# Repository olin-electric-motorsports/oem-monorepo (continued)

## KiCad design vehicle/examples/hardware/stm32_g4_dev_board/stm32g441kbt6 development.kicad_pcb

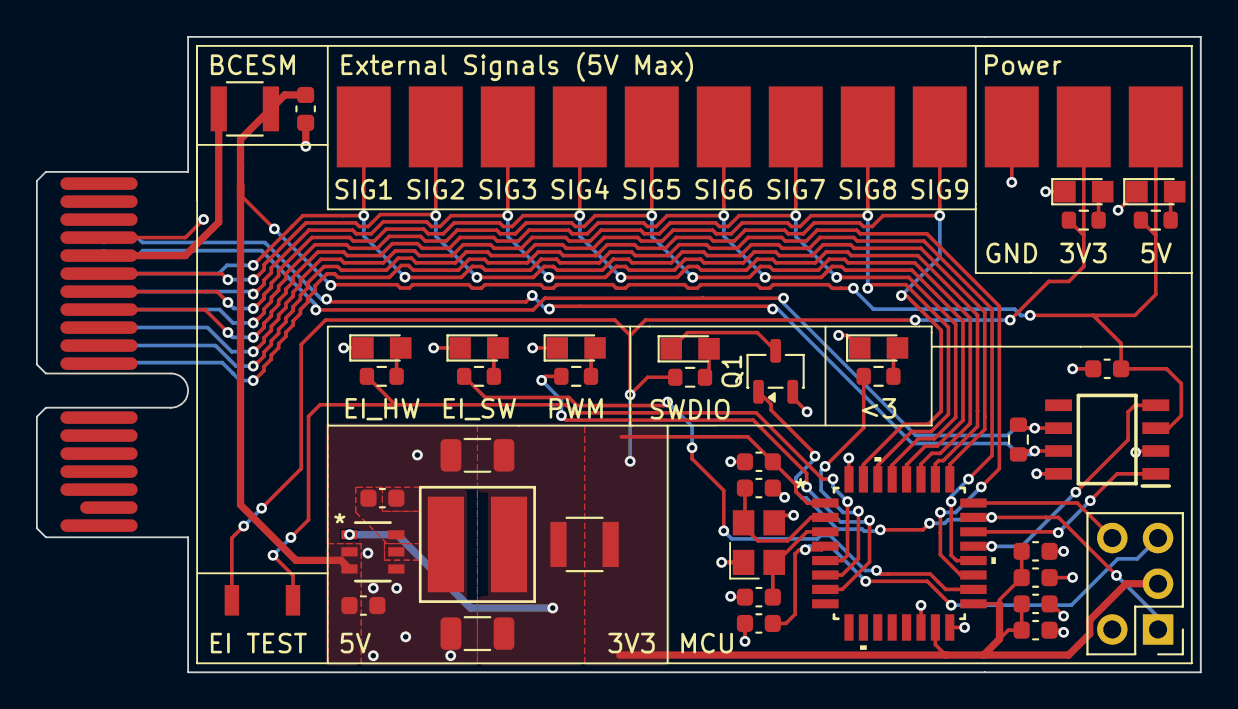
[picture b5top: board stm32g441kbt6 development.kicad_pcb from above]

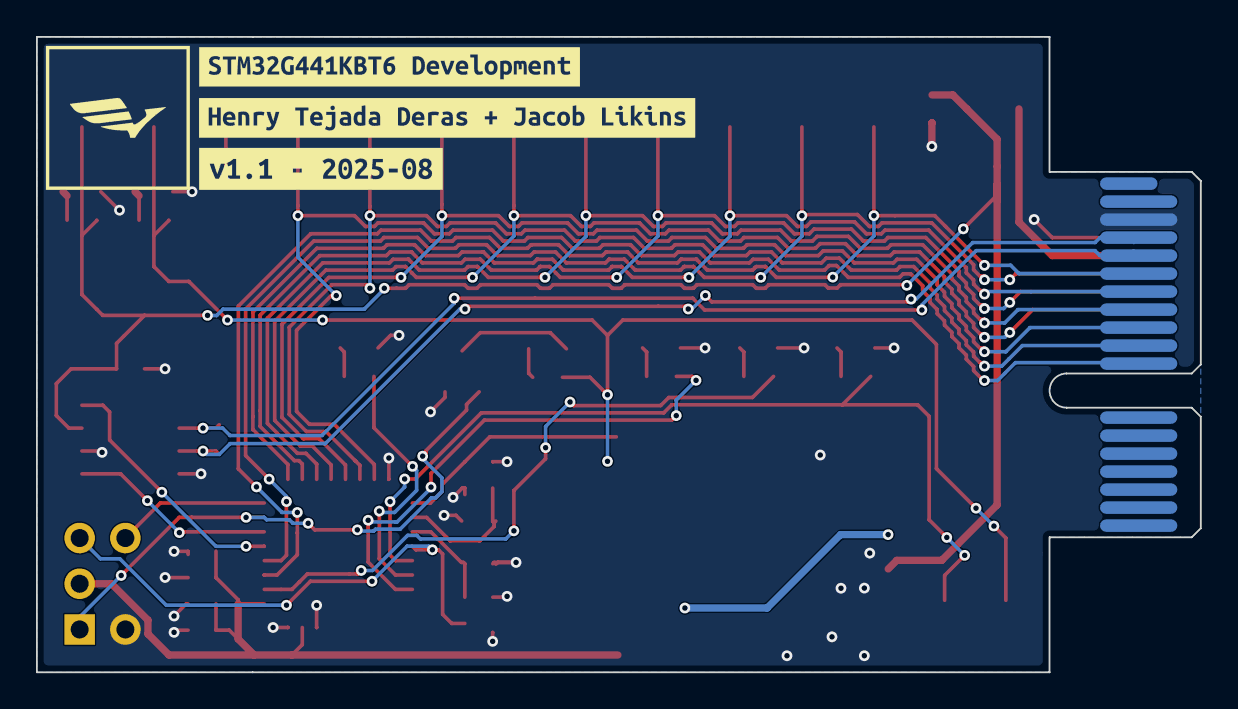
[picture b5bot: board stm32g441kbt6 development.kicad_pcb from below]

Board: 2 copper layers, 64.7 x 35.3 mm, 55 parts (3 on the bottom side), 37 nets.

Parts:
C1, C2, C5, C6, C11: C_0.1uF; C_0603
C3: C_10nF; C_0603
C4: C_1uF; C_0603
C7: C_4.7uF; C_0603
C8, C12: C_10uF; C_0603
C9, C10: C_22uF; C_1206_3216Metric
C13, C14: C_30pF; C_0603
D1: 3V3 POWER; CHIPLED_0805
D2: 5V POWER; CHIPLED_0805
D3: HEARTBEAT; CHIPLED_0805
D5: SWDIO; CHIPLED_0805
D6: INTERRUPT_TEST_HW; CHIPLED_0805
D7: INTERRUPT_TEST_SW; CHIPLED_0805
D8: PWM_TEST; CHIPLED_0805
F1, F2: F_500mA_16V; Fuse_1210
J1: CONN_pcie_x1; pcie_x1
J2: Programming_Pin_Header; Programming_Pin_Header_Keyed
L1: L_3.9uH; IND_BOURNS_SRR5018
Q1: BSS138; SOT-23-3
R1: R_120; R_0603
R2, R3, R4, R6, R7, R8, R9: R_1K; R_0603
SW1: INTERRUPT TEST SWITCH; SW_B3U-1000P_4.2x1.7mm
TP1: 3V3; Test_Point_SMD
TP2: 5V; Test_Point_SMD
TP3: EXT_SIG_1; Test_Point_SMD
TP4: EXT_SIG_2; Test_Point_SMD
TP5: EXT_SIG_3; Test_Point_SMD
TP6: EXT_SIG_4; Test_Point_SMD
TP7: EXT_SIG_5; Test_Point_SMD
TP8: EXT_SIG_6; Test_Point_SMD
TP9: EXT_SIG_7; Test_Point_SMD
TP10: EXT_SIG_8; Test_Point_SMD
TP11: EXT_SIG_9; Test_Point_SMD
TP12: GND; Test_Point_SMD
U1: STM32G441KBT6
U2: MCP2561-E_SN; SOIC127P600X175-8N
U3: AP63203WU-7; AP63203WU-7_DIO
Y1: X_Crystal_16MHz_18pF; Crystal_TXC7M
kibuzzard-68A62DAB: G***; kibuzzard-68A62DAB
kibuzzard-68A62DD1: G***; kibuzzard-68A62DD1
kibuzzard-68A78CB4: G***; kibuzzard-68A78CB4

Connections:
+3V3: C3.1, C4.1, C5.1, C6.1, C7.1, F2.2, J2.3, R2.1, R6.1, SW1.1, TP1.1, U1.1 (VDD), U1.15 (VDDA), U1.17 (VDD)
+5V: C1.2, C8.1, C12.1, F1.1, R3.1, TP2.1, U2.3 (VDD), U3.2 (EN), U3.3 (VIN)
/CAN_+: J1.A4 (CAN+), R1.1, U2.7 (CANH)
/CAN_-: J1.A5 (CAN-), R1.2, U2.6 (CANL)
/CAN_RX: U1.21 ((FDCAN1_RX/GPIO_EXTI11)PA11), U2.4 (RXD)
/CAN_TX: U1.22 ((FDCAN1_TX/GPIO_EXTI12)PA12), U2.1 (TXD)
/EXTERNAL_SIGNAL_1: J1.A6 (io_0), TP3.1, U1.19 ((TIM2_CH3/TIM15_BKIN/USART1_TX/GPIO_EXT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)
/EXTERNAL_SIGNAL_2: J1.B6 (io_1), TP4.1, U1.20 ((TIM2_CH4/USART1_RX/TIM17_BKIN/GPIO_EXT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)
/EXTERNAL_SIGNAL_3: J1.A7 (io_2), TP5.1, U1.25 ((TIM2_ETR/TIM2_CH1/GPIO_EXTI15)PA15)
/EXTERNAL_SIGNAL_4: J1.B7 (io_3), TP6.1, U1.26 ((TIM3_ETR/SPI1_SCK/TIM4_ETR/TIM2_CH2/GP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)
/EXTERNAL_SIGNAL_5: J1.A8 (io_4), TP7.1, U1.27 ((TIM17_BKIN/SPI1_MISO/TIM3_CH1/TIM16_CH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)
/EXTERNAL_SIGNAL_6: J1.B8 (io_5), TP8.1, U1.28 ((TIM17_CH1/SPI1_MOSI/TIM3_CH2/TIM16_BKI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)
/EXTERNAL_SIGNAL_7: J1.A9 (io_6), TP9.1, U1.29 ((TIM4_CH1/TIM16_CH1N/GPIO_EXTI6)PB6)
/EXTERNAL_SIGNAL_8: J1.A10 (io_8), TP10.1, U1.30 ((TIM3_CH4/TIM4_CH2/TIM17_CH1N/GPIO_EXTI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)
/EXTERNAL_SIGNAL_9: J1.A11 (io_10), TP11.1, U1.31 ((TIM4_CH3/TIM16_CH1/GPIO_EXTI8)PB8-BOOT0)
/HEARTBEAT: R4.1, U1.6 ((TIM15_CH1N/TIM2_CH2/GPIO_EXTI1/ADC2_IN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)
/INTERRUPT_TEST_HW: R7.1, SW1.2, U1.5 ((TIM2_ETR/TIM2_CH1/GPIO_EXTI0/ADC2_IN1/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)
/INTERRUPT_TEST_SW: R8.1, U1.18 ((TIM4_ETR/USART1_CK/GPIO_EXTI8)PA8)
/NRST: C2.1, J2.4, U1.4 ((GPIO_EXTI10)PG10-NRST)
/PWM_TEST: R9.1, U1.7 ((TIM15_CH1/USART2_TX/TIM2_CH3/GPIO_EXTI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)
/SWCLK: J2.5, U1.24 ((SYS_JTCK-SWCLK/GPIO_EXTI14)PA14)
/SWDIO: J2.1, Q1.1 (G), U1.23 ((SYS_JTMS-SWDIO/GPIO_EXTI13)PA13)
GND: C1.1, C2.2, C3.2, C4.2, C5.2, C6.2, C7.2, C8.2, C9.2, C10.2, C12.2, C13.2, C14.2, D1.1 (K), D2.1 (K), D3.1 (K), D6.1 (K), D7.1 (K), D8.1 (K), J1.A3 (GND), J1.B4 (GND), J2.2, Q1.2 (S), TP12.1, U1.14 (VSSA), U1.16 (VSS), U1.32 (VSS), U2.2 (VSS), U2.8 (STBY), U3.4 (GND), Y1.2, Y1.4
unnamed: D1.2 (A), R2.2
unnamed: D2.2 (A), R3.2
unnamed: D3.2 (A), R4.2
unnamed: D5.2 (A), R6.2
unnamed: D5.1 (K), Q1.3 (D)
unnamed: D6.2 (A), R7.2
unnamed: D7.2 (A), R8.2
unnamed: D8.2 (A), R9.2
unnamed: F1.2, J1.B5 (5V)
unnamed: C13.1, U1.2 (PF0-OSC_IN), Y1.3
unnamed: C14.1, U1.3 (PF1-OSC_OUT), Y1.1
unnamed: C11.1, U3.6 (BST)
unnamed: C9.1, C10.1, F2.1, L1.2, U3.1 (FB)
unnamed: C11.2, L1.1, U3.5 (SW)

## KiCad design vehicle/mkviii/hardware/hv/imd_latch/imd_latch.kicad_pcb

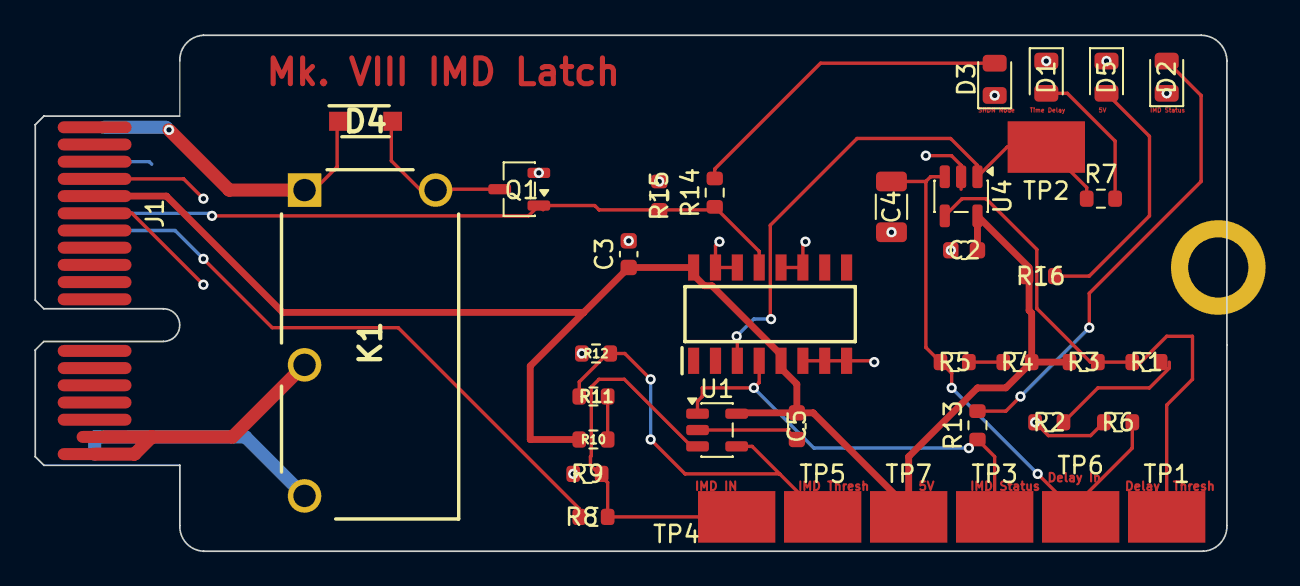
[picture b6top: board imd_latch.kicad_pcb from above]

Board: 2 copper layers, 69.3 x 30.0 mm, 38 parts (0 on the bottom side), 21 nets.

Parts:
C2, C3, C5: C_0.1uF; C_0603_1608Metric
C4: C_22uF; C_1206_3216Metric
D1, D2, D3: D_Red_LED; D_0805_2012Metric
D4: D_100V_1A; SODFL3718X102N (D_Schottky_100V_1A_SMD - SS110LW)
D5: LED; D_0805_2012Metric
J1: J_PCIe_x1; J_PCIe_x1_Key
K1: K_10A_5V; G5Q1A4DC5 (K_SPST-NO_10A_5V_TH - G5Q-1A4-DC5)
Q1: SSM3K333R,LF; SOT-23-3
R1, R2, R3, R10, R11, R12: R_100k_0.1W; R_0603_1608Metric
R4: R_71.5k_0.1W; R_0603_1608Metric
R5: R_120k_0.1W; R_0603_1608Metric
R6: R_1.82M_0.1W; R_0603_1608Metric
R7, R9: R_1k_0.1W; R_0603_1608Metric
R8: R_3k_0.1W; R_0603_1608Metric
R13, R14: R_1k; R_0603_1608Metric
R15: R_604k_0.1W; R_0603_1608Metric
R16: R_330; R_0603_1608Metric
TP1, TP2, TP3, TP4, TP5, TP6, TP7: TP_SMD; TP_Hook_SMD
U1, U4: MCP6001UT-I/OT; SOT-23-5
U3: CD4044BDR; SOIC127P600X175-16N (U_Quad-NAND-RS-Latch_CD4044BDR_16-SOIC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

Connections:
+5V: C2.1, C3.1, C5.2, J1.B5 (5V), R3.1, R4.1, R10.2, R16.2, TP7.1, U1.5 (V+), U3.5 (ENABLE), U3.16 (VDD), U4.5 (V+)
+BATT: D4.1 (K), J1.A1 (12V/3V(DA_ONLY)), K1.1
/<NO NET>: J1.A7 (io_2), R8.1
/IMD_STATUS: J1.A6 (io_0), Q1.1 (G), R14.1, R15.1, U3.13 (Q1)
/IMD_status_output: R13.1, TP3.1, U1.1, U3.4 (RI)
/SHDN_IN: J1.A17 (SHDN_IN/io_22), J1.A18 (SHDN_IN/io_24), K1.3
/SHDN_OUT: J1.B17 (SHDN_OUT/io_23), J1.B18 (SHDN_OUT/io_25), K1.2
/Time_delay: R7.1, TP2.1, U3.3 (SI), U4.1
GND: C2.2, C3.2, C4.2, C5.1, D1.1 (K), D2.1 (K), D3.1 (K), D5.1 (K), J1.A3 (GND), J1.B4 (GND), J1.B6 (io_1), Q1.2 (S), R2.1, R6.2, R9.2, R12.1, R15.2, U1.2 (V-), U3.6 (R2), U3.7 (S2), U3.8 (VSS), U3.11 (S3), U3.12 (R3), U3.14 (R4), U3.15 (S4), U4.2 (V-)
unnamed: D1.2 (A), R7.2
unnamed: D2.2 (A), R13.2
unnamed: D3.2 (A), R14.2
unnamed: D4.2 (A), K1.5, Q1.3 (D)
unnamed: D5.2 (A), R16.1
unnamed: R1.1, R2.2
unnamed: R4.2, R5.1
unnamed: R10.1, R11.2
unnamed: R8.2, R9.1, TP4.1, U1.3 (+)
unnamed: R11.1, R12.2, TP5.1, U1.4 (-)
unnamed: C4.1, R5.2, R6.1, TP6.1, U4.3 (+)
unnamed: R1.2, R3.2, TP1.1, U4.4 (-)

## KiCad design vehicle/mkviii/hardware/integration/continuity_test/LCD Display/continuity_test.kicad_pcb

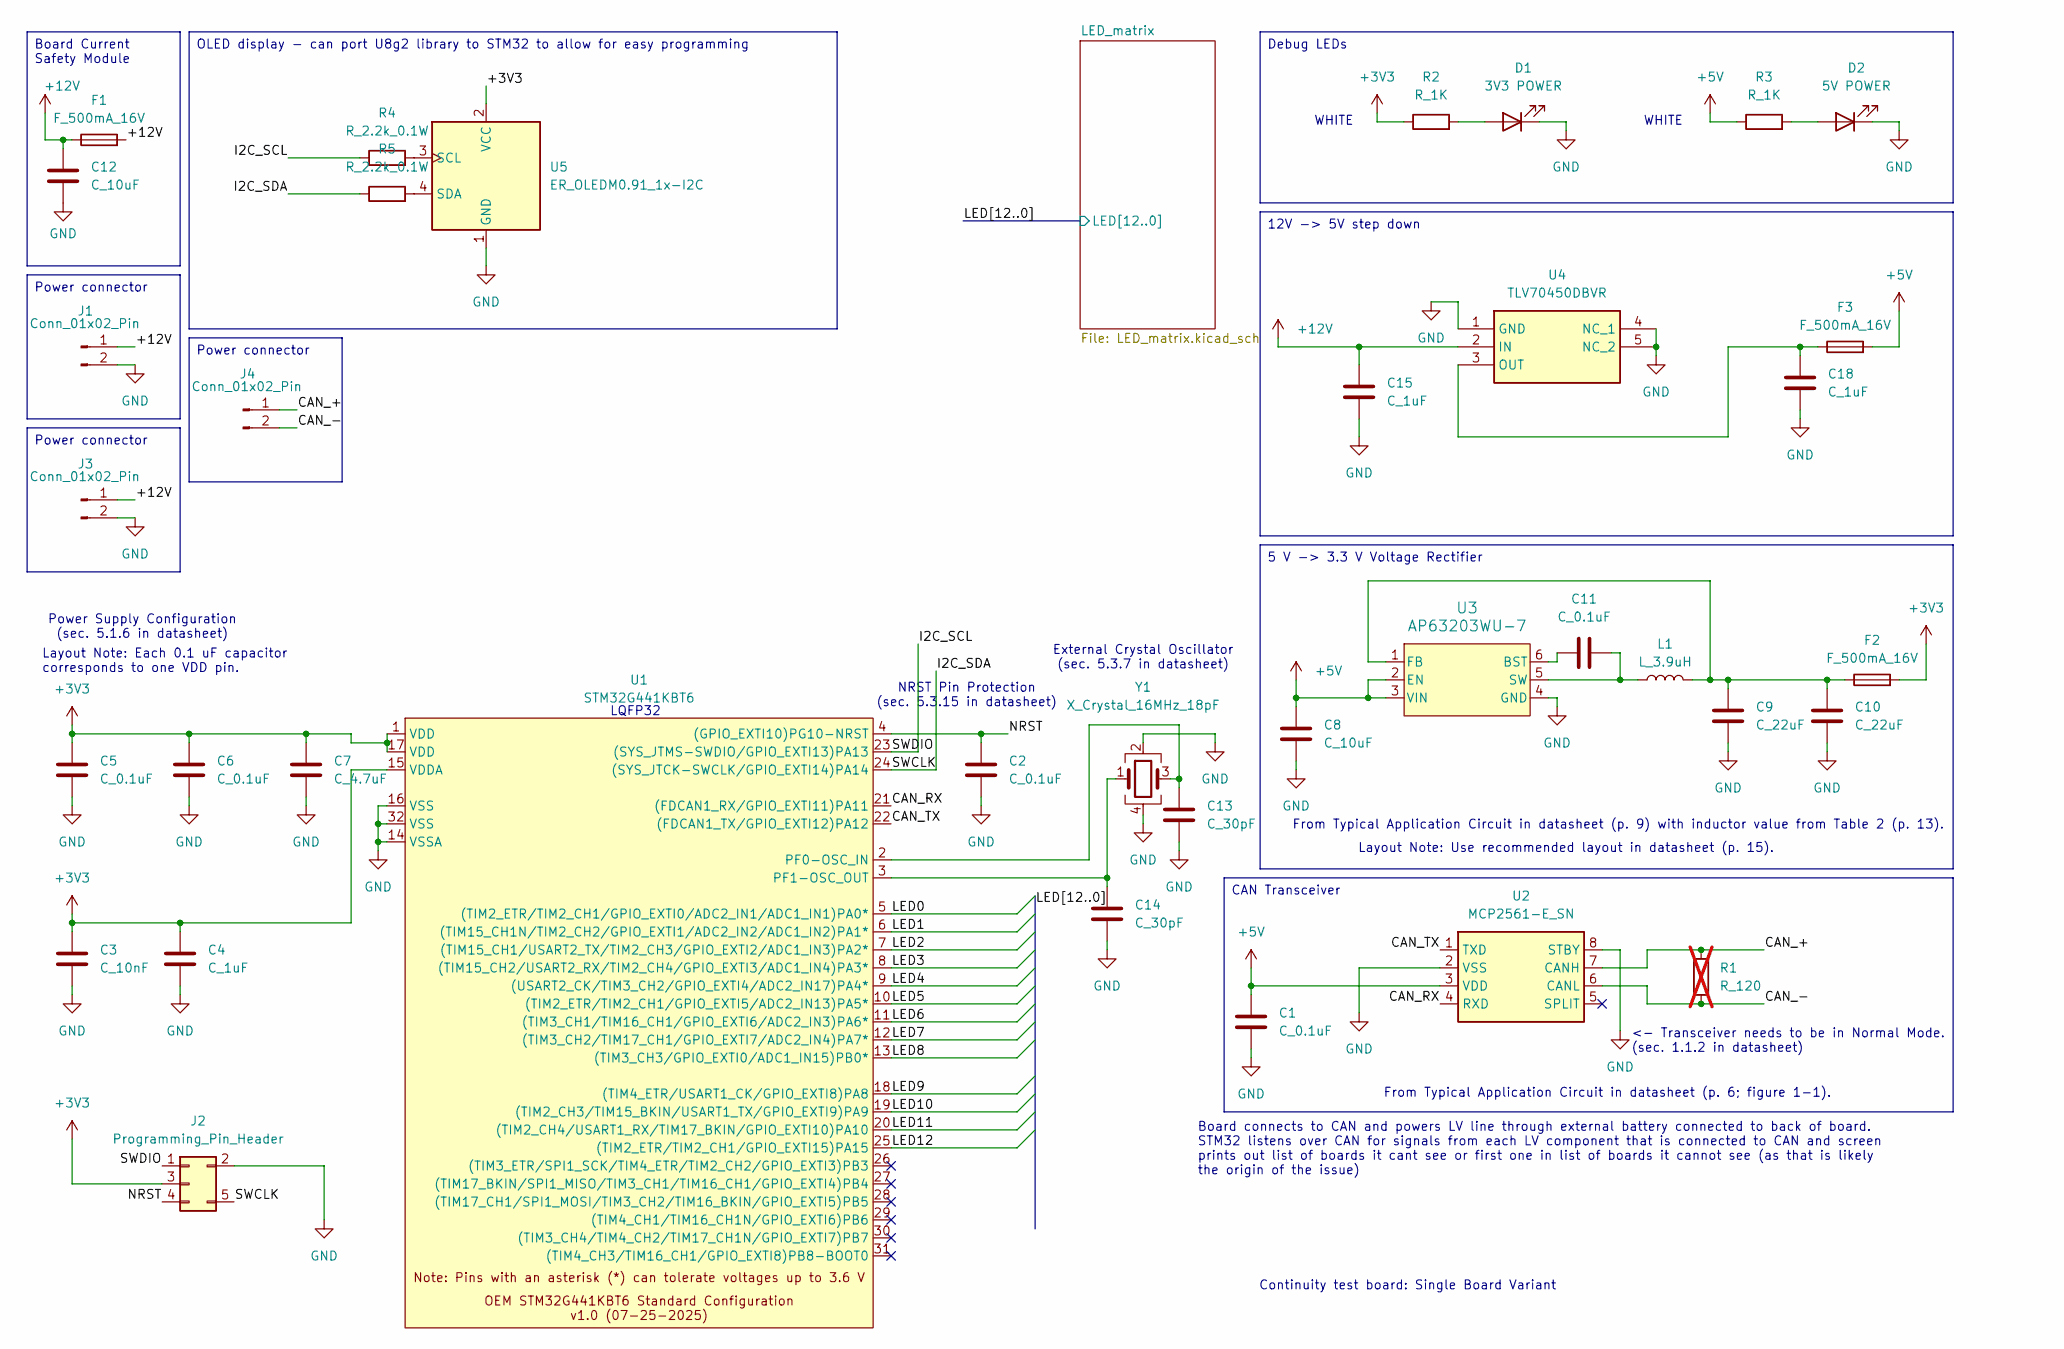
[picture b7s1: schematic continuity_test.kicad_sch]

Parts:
C1, C2, C5, C6, C11: C_0.1uF; C_0603_1608Metric; MPN CL10B104KB8NNWC
C3: C_10nF; C_0603_1608Metric; MPN CL10B103KB8NNNC
C4: C_1uF; C_0603_1608Metric; MPN CL10B105KA8NNNC
C7: C_4.7uF; C_0603_1608Metric; MPN GRT188R61E475ME13D
C8, C12: C_10uF; C_0603_1608Metric; MPN LMK107BBJ106KALT
C9, C10: C_22uF; C_1206_3216Metric; MPN CL31A226KAHNNNE
C13, C14: C_30pF; C_0603_1608Metric; MPN CML0603C0G300JT50V
C15: C_1uF; C_0603_1608Metric; MPN LMK107BBJ106KALT
C18: C_1uF; C_1206_3216Metric; MPN CL31A226KAHNNNE
D1: 3V3 POWER; D_0805_2012Metric; MPN B1701TW--20P000314U1930
D2: 5V POWER; D_0805_2012Metric; MPN B1701TW--20P000314U1930
F1, F2, F3: F_500mA_16V; Fuse_1210_3225Metric; MPN 0ZCH0050FF2G
J1, J3, J4: Conn_01x02_Pin; Molex_Micro-Fit_3.0_43045-0412_2x02_P3.00mm_Vertical
J2: Programming_Pin_Header; J_Programming_Pin_Header_Keyed
L1: L_3.9uH; IND_BOURNS_SRR5018 (L_3.9uH_2A_55m_SMD)
R1: R_120; R_0603_1608Metric; MPN RC0603FR-13120RL; not fitted
R2, R3: R_1K; R_0603_1608Metric; MPN RMCF0603FT1K00
R4, R5: R_2.2k_0.1W; R_0603_1608Metric; MPN WR06X222 JTL
U1: STM32G441KBT6; LQFP-32_7x7mm_P0.8mm
U2: MCP2561-E_SN; U_1.222V-Buck-Conv_RT6285GSP_ SOP-8; Mouser Part Number 579-MCP2561-E/SN
U3: AP63203WU-7; SOT-23-6
U4: TLV70450DBVR; SOT-23-5; MPN TLV70450DBVR
U5: ER_OLEDM0.91_1x-I2C
Y1: X_Crystal_16MHz_18pF; FA238160000MBC0 (X_16MHz_18pF_SMD - FA-238_16.0000MB-C0); MPN 7M-16.000MAAJ-T

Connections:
+3V3: C3.1, C4.1, C5.1, C6.1, C7.1, F2.2, J2.3, R2.1, U1.1 (VDD), U1.15 (VDDA), U1.17 (VDD), U5.2 (VCC)
+5V: C1.2, C8.1, F3.2, R3.1, U2.3 (VDD), U3.2 (EN), U3.3 (VIN)
+12V: C12.1, C15.1, F1.1, F1.2, J1.1, J3.1, U4.2 (IN)
/CAN_+: J4.1, R1.1, U2.7 (CANH)
/CAN_-: J4.2, R1.2, U2.6 (CANL)
/CAN_RX: U1.21 ((FDCAN1_RX/GPIO_EXTI11)PA11), U2.4 (RXD)
/CAN_TX: U1.22 ((FDCAN1_TX/GPIO_EXTI12)PA12), U2.1 (TXD)
/I2C_SCL: J2.1, R4.1, U1.23 ((SYS_JTMS-SWDIO/GPIO_EXTI13)PA13)
/I2C_SDA: J2.5, R5.1, U1.24 ((SYS_JTCK-SWCLK/GPIO_EXTI14)PA14)
/LED0: U1.5 ((TIM2_ETR/TIM2_CH1/GPIO_EXTI0/ADC2_IN1/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); also elsewhere on the board
/LED1: U1.6 ((TIM15_CH1N/TIM2_CH2/GPIO_EXTI1/ADC2_IN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); also elsewhere on the board
/LED2: U1.7 ((TIM15_CH1/USART2_TX/TIM2_CH3/GPIO_EXTI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); also elsewhere on the board
/LED3: U1.8 ((TIM15_CH2/USART2_RX/TIM2_CH4/GPIO_EXTI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); also elsewhere on the board
/LED4: U1.9 ((USART2_CK/TIM3_CH2/GPIO_EXTI4/ADC2_IN1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); also elsewhere on the board
/LED5: U1.10 ((TIM2_ETR/TIM2_CH1/GPIO_EXTI5/ADC2_IN13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); also elsewhere on the board
/LED6: U1.11 ((TIM3_CH1/TIM16_CH1/GPIO_EXTI6/ADC2_IN3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); also elsewhere on the board
/LED7: U1.12 ((TIM3_CH2/TIM17_CH1/GPIO_EXTI7/ADC2_IN4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); also elsewhere on the board
/LED8: U1.13 ((TIM3_CH3/GPIO_EXTI0/ADC1_IN15)PB0*); also elsewhere on the board
/LED9: U1.18 ((TIM4_ETR/USART1_CK/GPIO_EXTI8)PA8); also elsewhere on the board
/LED10: U1.19 ((TIM2_CH3/TIM15_BKIN/USART1_TX/GPIO_EXT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); also elsewhere on the board
/LED11: U1.20 ((TIM2_CH4/USART1_RX/TIM17_BKIN/GPIO_EXT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); also elsewhere on the board
/LED12: U1.25 ((TIM2_ETR/TIM2_CH1/GPIO_EXTI15)PA15); also elsewhere on the board
/NRST: C2.1, J2.4, U1.4 ((GPIO_EXTI10)PG10-NRST)
GND: C1.1, C2.2, C3.2, C4.2, C5.2, C6.2, C7.2, C8.2, C9.2, C10.2, C12.2, C13.2, C14.2, C15.2, C18.2, D1.1 (K), D2.1 (K), J1.2, J2.2, J3.2, U1.14 (VSSA), U1.16 (VSS), U1.32 (VSS), U2.2 (VSS), U2.8 (STBY), U3.4 (GND), U4.1 (GND), U4.4 (NC_1), U4.5 (NC_2), U5.1 (GND), Y1.2, Y1.4; also elsewhere on the board
unnamed 24: D1.2 (A), R2.2; also elsewhere on the board
unnamed 25: D2.2 (A), R3.2; also elsewhere on the board
unnamed: C13.1, U1.2 (PF0-OSC_IN), Y1.3
unnamed: C14.1, U1.3 (PF1-OSC_OUT), Y1.1
unnamed: C11.1, U3.6 (BST)
unnamed: C9.1, C10.1, F2.1, L1.2, U3.1 (FB)
unnamed: C11.2, L1.1, U3.5 (SW)
unnamed: C18.1, F3.1, U4.3 (OUT)
unnamed: R4.2, U5.3 (SCL)
unnamed: R5.2, U5.4 (SDA)

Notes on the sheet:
From Typical Application Circuit in datasheet (p. 9) with inductor value from Table 2 (p. 13).
Layout Note: Each 0.1 uF capacitor corresponds to one VDD pin.
WHITE
NRST Pin Protection (sec. 5.3.15 in datasheet)
External Crystal Oscillator (sec. 5.3.7 in datasheet)
Power Supply Configuration (sec. 5.1.6 in datasheet)
Board connects to CAN and powers LV line through external battery connected to back of board. STM32 listens over CAN for signals from each LV component that is connected to CAN and screen prints out list of boards it cant see or first one in list of boards it cannot see (as that is likely the origi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
LQFP32
Layout Note: Use recommended layout in datasheet (p. 15).
<- Transceiver needs to be in Normal Mode. (sec. 1.1.2 in datasheet)
From Typical Application Circuit in datasheet (p. 6; figure 1-1).
Continuity test board: Single Board Variant
12V -> 5V step down
CAN Transceiver
5 V -> 3.3 V Voltage Rectifier
Power connector
OLED display - can port U8g2 library to STM32 to allow for easy programming
Debug LEDs
Board Current Safety Module

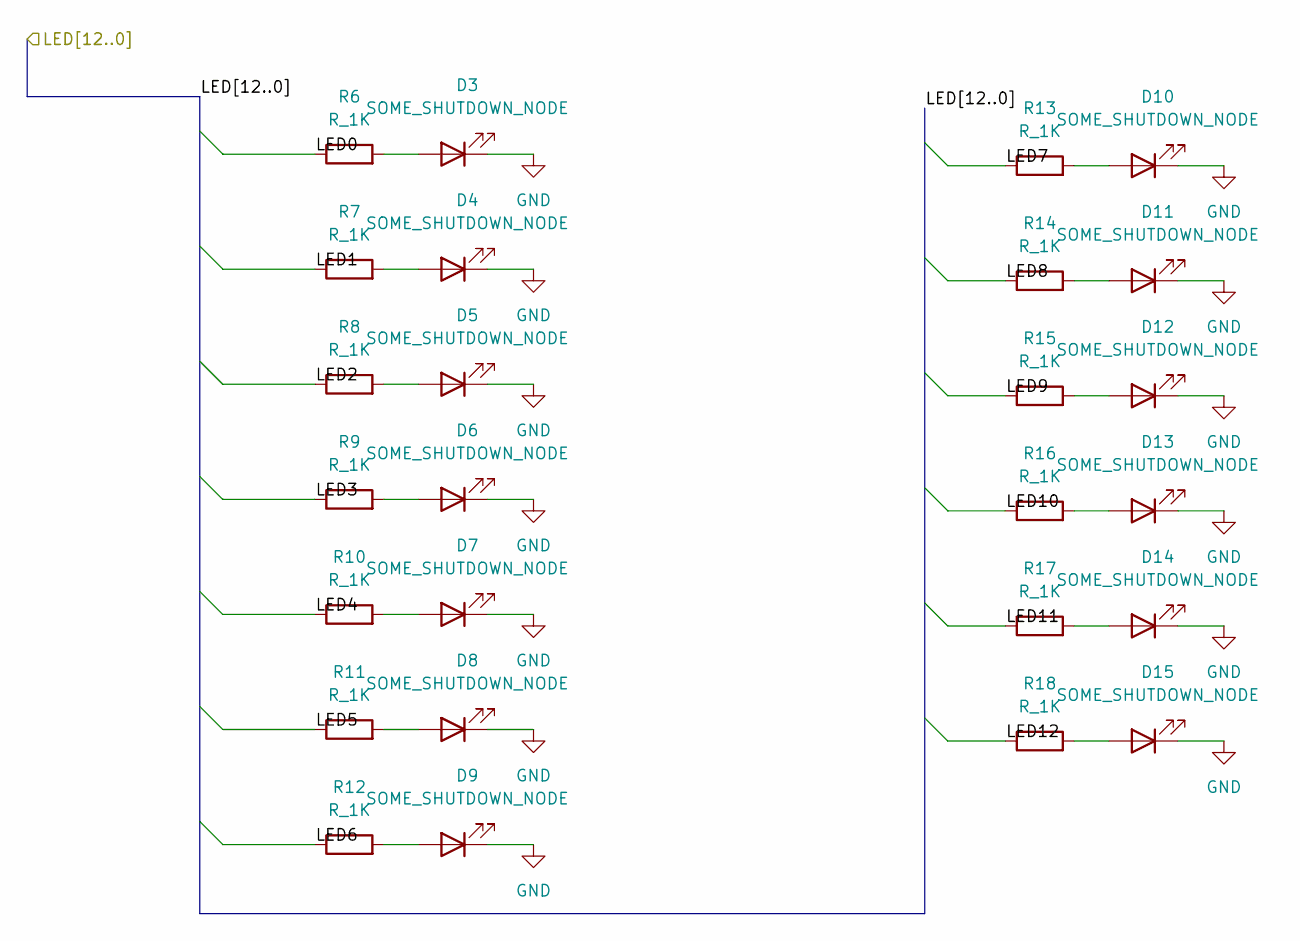
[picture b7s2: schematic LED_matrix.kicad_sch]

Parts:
D3, D4, D5, D6, D7, D8, D9, D10, D11, D12, D13, D14, D15: SOME_SHUTDOWN_NODE; D_0805_2012Metric; MPN B1701TW--20P000314U1930
R6, R7, R8, R9, R10, R11, R12, R13, R14, R15, R16, R17, R18: R_1K; R_0603_1608Metric; MPN RMCF0603FT1K00

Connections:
/LED0: R6.1; also elsewhere on the board
/LED1: R7.1; also elsewhere on the board
/LED2: R8.1; also elsewhere on the board
/LED3: R9.1; also elsewhere on the board
/LED4: R10.1; also elsewhere on the board
/LED5: R11.1; also elsewhere on the board
/LED6: R12.1; also elsewhere on the board
/LED7: R13.1; also elsewhere on the board
/LED8: R14.1; also elsewhere on the board
/LED9: R15.1; also elsewhere on the board
/LED10: R16.1; also elsewhere on the board
/LED11: R17.1; also elsewhere on the board
/LED12: R18.1; also elsewhere on the board
GND: D3.1 (K), D4.1 (K), D5.1 (K), D6.1 (K), D7.1 (K), D8.1 (K), D9.1 (K), D10.1 (K), D11.1 (K), D12.1 (K), D13.1 (K), D14.1 (K), D15.1 (K); also elsewhere on the board
unnamed: D3.2 (A), R6.2
unnamed: D4.2 (A), R7.2
unnamed: D5.2 (A), R8.2
unnamed: D6.2 (A), R9.2
unnamed: D7.2 (A), R10.2
unnamed: D8.2 (A), R11.2
unnamed: D9.2 (A), R12.2
unnamed: D10.2 (A), R13.2
unnamed: D11.2 (A), R14.2
unnamed: D12.2 (A), R15.2
unnamed: D13.2 (A), R16.2
unnamed: D14.2 (A), R17.2
unnamed: D15.2 (A), R18.2

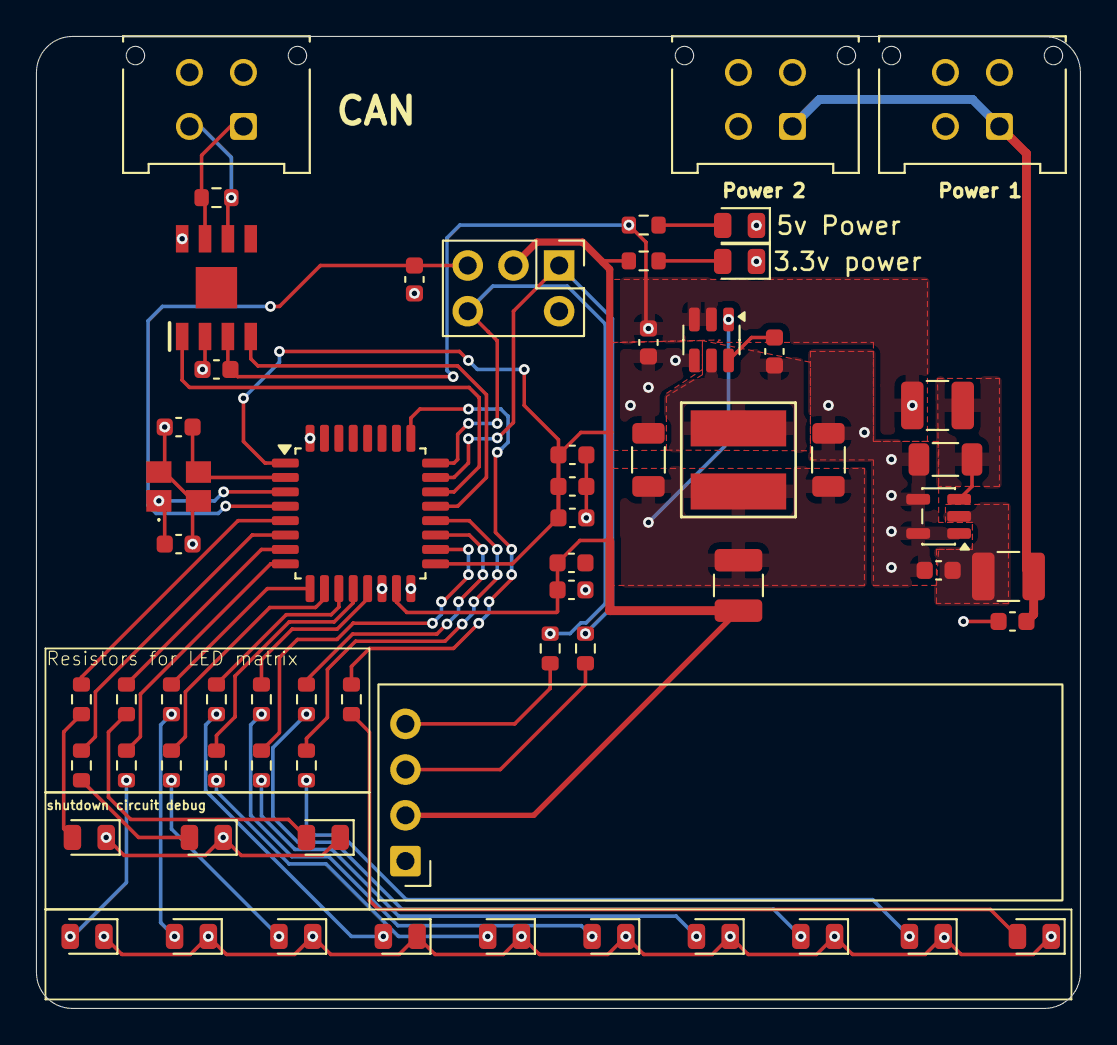
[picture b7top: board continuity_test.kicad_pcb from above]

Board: 2 copper layers, 58.0 x 54.0 mm, 63 parts (0 on the bottom side), 47 nets.

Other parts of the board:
3.3v power: 3V3 POWER; D_0805_2012Metric
5v Power: 5V POWER; D_0805_2012Metric

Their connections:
GND: 3.3v power.1 (K), 5v Power.1 (K); also elsewhere on the board
unnamed 24: 3.3v power.2 (A); also elsewhere on the board
unnamed 25: 5v Power.2 (A); also elsewhere on the board

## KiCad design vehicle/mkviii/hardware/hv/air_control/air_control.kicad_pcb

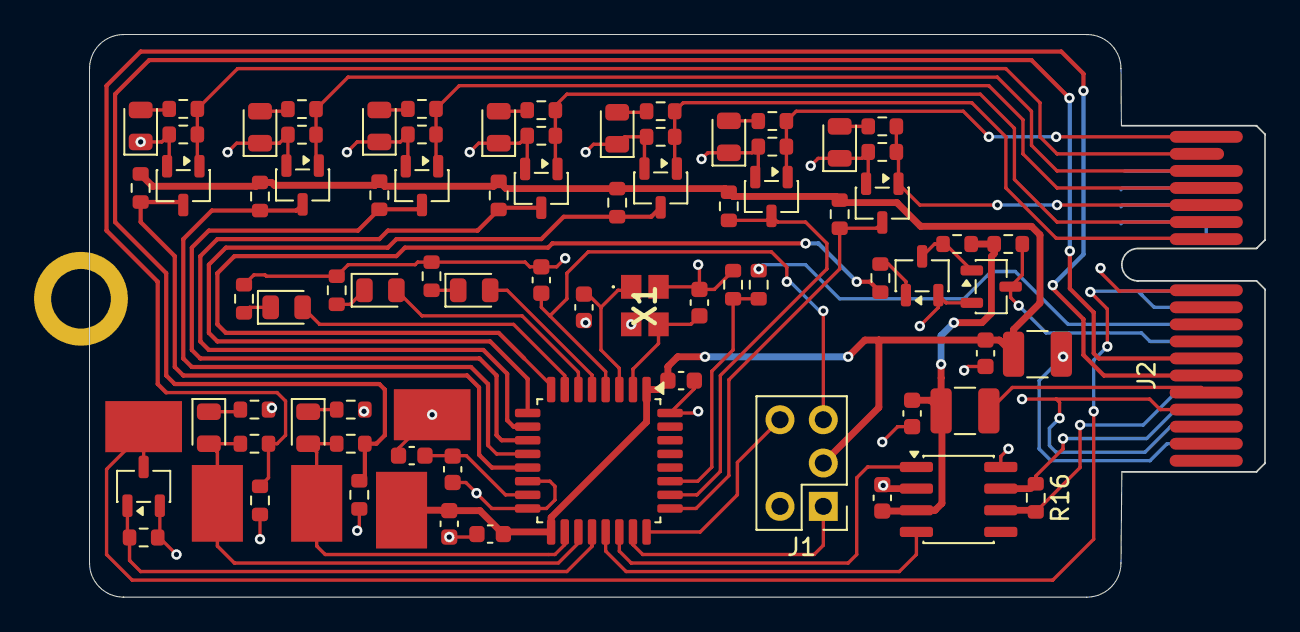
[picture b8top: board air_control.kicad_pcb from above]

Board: 2 copper layers, 68.9 x 33.0 mm, 83 parts (0 on the bottom side), 56 nets.

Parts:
C1, C2: C_10uF; C_0603_1608Metric
C3: C_4.7uF; C_0603_1608Metric
C4: C_10nF; C_0603_1608Metric
C5, C7, C9, C11: C_0.1uF; C_0603_1608Metric
C6: C_1uF; C_0603_1608Metric
C8, C10: C_30pF; C_0603_1608Metric
D1: D_Red_LED; D_0805_2012Metric
D2, D3, D4, D5: D_Amber_LED; D_0805_2012Metric
D6, D7, D8, D9, D10, D11, D12: D_Blue_LED; D_0805_2012Metric
F1, F2: F_500mA_16V; Fuse_1210_3225Metric
H1: H_MountingHole
J1: J_Programming_Pin_Header; J_Programming_Pin_Header_Keyed
J2: J_PCIe_x1; J_PCIe_x1_Key
Q1, Q2, Q3, Q4, Q5, Q6, Q7, Q8, Q9, Q10: SSM3K333R,LF; SOT-23-3
R1, R7, R13: R_5.1k; R_0603_1608Metric
R2, R8, R10, R11, R14, R17, R20, R23, R26, R29, R32, R35: R_10k; R_0603_1608Metric
R3, R4, R5, R6, R9, R12, R15: R_1k; R_0603_1608Metric
R16: R_120; R_0603_1608Metric
R18, R21, R24, R27, R30, R33, R36: R_100k; R_0603_1608Metric
R19, R22, R25, R28, R31, R34, R37: R_3k; R_0603_1608Metric
TP1, TP2, TP3, TP4, TP5: TP_SMD; TP_Hook_SMD
U1: STM32G441KBT6; LQFP-32_7x7mm_P0.8mm
U2: MCP2561-E_SN; SOIC-8_3.9x4.9mm_P1.27mm
X1: X_16MHz_18pF; FA238160000MBC0 (X_16MHz_18pF_SMD - FA-238_16.0000MB-C0)

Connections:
+3.3V: C1.1, C3.1, C5.1, C7.1, F1.1, J1.3, R17.1, R20.1, R23.1, R26.1, R29.1, R32.1, R35.1, TP1.1, U1.1 (VDD), U1.17 (VDD)
+3V3: C4.1, C6.1, U1.15 (VDDA)
+5V: C2.1, C11.1, F2.1, R10.1, R11.1, U2.3 (VDD)
/AIR+_LSD_OUT: J2.A10 (io_8), J2.A11 (io_10), Q3.3 (D), TP5.1
/AIR+_WELD_DETECT_IN: D4.2 (A), R7.2, TP3.1, U1.19 ((TIM2_CH3/TIM15_BKIN/USART1_TX/GPIO_EXT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)
/AIR+_WELD_DETECT_OUT: J2.B6 (io_1), R7.1, R8.1
/AIR-_LSD: Q3.1 (G), R15.1, U1.20 ((TIM2_CH4/USART1_RX/TIM17_BKIN/GPIO_EXT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)
/AIR-_WELD_DETECT_IN: D5.2 (A), R13.2, TP4.1, U1.18 ((TIM4_ETR/USART1_CK/GPIO_EXTI8)PA8)
/AIR-_WELD_DETECT_OUT: J2.B7 (io_3), R13.1, R14.1
/CAN_+: J2.A4 (CAN+), R16.1, U2.7 (CANH)
/CAN_-: J2.A5 (CAN-), R16.2, U2.6 (CANL)
/CAN_RX: U1.21 ((FDCAN1_RX/GPIO_EXTI11)PA11), U2.4 (RXD)
/CAN_TX: U1.22 ((FDCAN1_TX/GPIO_EXTI12)PA12), U2.1 (TXD)
/ERROR: D1.2 (A), U1.5 ((TIM2_ETR/TIM2_CH1/GPIO_EXTI0/ADC2_IN1/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)
/HEARTBEAT: D2.2 (A), U1.6 ((TIM15_CH1N/TIM2_CH2/GPIO_EXTI1/ADC2_IN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)
/IMD_SENSE: J2.A9 (io_6), R1.2
/IMD_SENSE_OUT: R1.1, R2.1, U1.27 ((TIM17_BKIN/SPI1_MISO/TIM3_CH1/TIM16_CH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)
/INIT: D3.2 (A), U1.7 ((TIM15_CH1/USART2_TX/TIM2_CH3/GPIO_EXTI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)
/NRST: C9.1, J1.4, U1.4 ((GPIO_EXTI10)PG10-NRST)
/PRECHARGE: J2.A8 (io_4), Q2.3 (D), R11.2
/PRECHARGE_IN: R9.2, U1.8 ((TIM15_CH2/USART2_RX/TIM2_CH4/GPIO_EXTI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)
/SHDN_SENSE_BMS: J2.B14 (io_17), Q6.1 (G), R24.1, R25.1
/SHDN_SENSE_BMS_OUT: Q6.3 (D), R23.2, U1.25 ((TIM2_ETR/TIM2_CH1/GPIO_EXTI15)PA15)
/SHDN_SENSE_EMETER: J2.B17 (SHDN_OUT/io_23), Q9.1 (G), R33.1, R34.1
/SHDN_SENSE_EMETER_OUT: Q9.3 (D), R32.2, U1.13 ((TIM3_CH3/GPIO_EXTI0/ADC1_IN15)PB0*)
/SHDN_SENSE_HVD: J2.B18 (SHDN_OUT/io_25), Q10.1 (G), R36.1, R37.1
/SHDN_SENSE_HVD_OUT: Q10.3 (D), R35.2, U1.26 ((TIM3_ETR/SPI1_SCK/TIM4_ETR/TIM2_CH2/GP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)
/SHDN_SENSE_IMD: J2.B13 (io_15), Q7.1 (G), R27.1, R28.1
/SHDN_SENSE_IMD_OUT: Q7.3 (D), R26.2, U1.10 ((TIM2_ETR/TIM2_CH1/GPIO_EXTI5/ADC2_IN13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)
/SHDN_SENSE_MPC: J2.B15 (io_19), Q5.1 (G), R21.1, R22.1
/SHDN_SENSE_MPC_OUT: Q5.3 (D), R20.2, U1.11 ((TIM3_CH1/TIM16_CH1/GPIO_EXTI6/ADC2_IN3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)
/SHDN_SENSE_TSMP: J2.B16 (io_21), Q4.1 (G), R18.1, R19.1
/SHDN_SENSE_TSMP_OUT: Q4.3 (D), R17.2, U1.12 ((TIM3_CH2/TIM17_CH1/GPIO_EXTI7/ADC2_IN4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)
/SHDN_SENSE_TSMS: J2.B12 (io_13), Q8.1 (G), R30.1, R31.1
/SHDN_SENSE_TSMS_OUT: Q8.3 (D), R29.2, U1.9 ((USART2_CK/TIM3_CH2/GPIO_EXTI4/ADC2_IN1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)
/SWCLK: J1.5, U1.24 ((SYS_JTCK-SWCLK/GPIO_EXTI14)PA14)
/SWDIO: J1.1, U1.23 ((SYS_JTMS-SWDIO/GPIO_EXTI13)PA13)
GND: C1.2, C2.2, C3.2, C4.2, C5.2, C6.2, C7.2, C8.2, C9.2, C10.2, C11.2, D6.1 (K), D7.1 (K), D8.1 (K), D9.1 (K), D10.1 (K), D11.1 (K), D12.1 (K), H1.1 (1_1), J1.2, J2.A3 (GND), J2.A12 (io_12), J2.A13 (io_14), J2.A14 (io_16), J2.A15 (io_18), J2.A16 (io_20), J2.B4 (GND), J2.B11 (io_11), Q1.2 (S), Q2.2 (S), Q3.2 (S), Q4.2 (S), Q5.2 (S), Q6.2 (S), Q7.2 (S), Q8.2 (S), Q9.2 (S), Q10.2 (S), R2.2, R3.2, R4.2, R5.2, R6.2, R8.2, R12.2, R14.2, R15.2, R18.2, R21.2, R24.2, R27.2, R30.2, R33.2, R36.2, TP2.1, U1.14 (VSSA), U1.16 (VSS), U1.32 (VSS), U2.2 (VSS), U2.8 (STBY), X1.2, X1.4
unnamed: D1.1 (K), R3.1
unnamed: D2.1 (K), R4.1
unnamed: D3.1 (K), R5.1
unnamed: D4.1 (K), R6.1
unnamed: D5.1 (K), R12.1
unnamed: D6.2 (A), R19.2
unnamed: D7.2 (A), R22.2
unnamed: D8.2 (A), R25.2
unnamed: D9.2 (A), R28.2
unnamed: D10.2 (A), R31.2
unnamed: D11.2 (A), R34.2
unnamed: D12.2 (A), R37.2
unnamed: F1.2, J2.A2 (12V/3V(DA_ONLY))
unnamed: F2.2, J2.B5 (5V)
unnamed: Q1.3 (D), Q2.1 (G), R10.2
unnamed: Q1.1 (G), R9.1
unnamed: C10.1, U1.2 (PF0-OSC_IN), X1.3
unnamed: C8.1, U1.3 (PF1-OSC_OUT), X1.1

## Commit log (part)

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2026-03-17 Added production files; rounded corners; added throttle power wire terminal
2026-03-17 importated cantool and will begin to work on DBC generation
2026-03-18 Prechrarge Discharge - Schematic Organized
2026-03-18 fully functioning dbc generator
2026-03-19 Added Onboarding Related Files
2026-03-20 Everything builds but there is no testing done yet, so now is just testing
2026-03-21 Correctly sending CAN messages but not recieving them from other boards on the CAR
2026-03-21 fully tested and integrated system for CAN, will need file clean up tho but everything is proven to work
2026-03-22 reorganized all the files into an easier way to merge things
2026-03-22 fixed all build errors
2026-03-23 fixed comments
2026-03-23 Formatting: rename example to blinky and move function implementations from source to header
2026-03-23 Small README changes
2026-03-23 CAN integration into the car with format changes
2026-03-27 Windows compatible repo
2026-03-31 Add adc lib first draft
2026-03-31 Add ADC library
2026-03-31 Add bazel files & update header documentation
2026-04-02 Add testing code for adc lib
2026-04-03 polish library and example code, ready to use
2026-04-04 Clean up of ADC library and fixed timing issues
2026-04-04 fixed build erros
2026-04-04 ADC library & example code
    Fully working ADC library to make using ADC pin easier. Also There was a sneaky fix for the clock so timing would actually be correct for everyones boards
2026-04-04 most up to data
2026-04-04 Final version of roadkill harness
2026-04-04 fixed error file
2026-04-04 Precharge-Discharge Board Schematics and PCB
2026-04-04 Update charging board integration
2026-04-04 Charging Board Schematics and PCB (#16)
2026-04-10 integrated sensor's api to help read sensor data. Got functions to read data, convert data into temperature, find average temperature, find the max temperature and find where that is. Also flags over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
2026-04-11 Fixed wrong resistor values for BMS DA SMBus; moved all files to the mkviii folder from mkiii
2026-04-11 Corrected Date on BMS DA Schematics
2026-04-11 Added Power-Thermistor PCB provided by Liam Fries with minor schematic changes (modified title block; added temperature sensor and connector)
2026-04-11 Added Production Files and updated PCB file to match PCB file used for production files.
2026-04-11 Power-Thermistor Schematics and PCB (#24)
2026-04-11 fixing files
2026-04-11 BMS Motherboard Schematics and PCB Layout (#19)
2026-04-11 fix file and bazel constrants
2026-04-11 initial setup for bms
2026-04-12 roadkill harness - 3 LED blinky code(works)
2026-04-12 can_api: Revise README for STM32 transition
2026-04-13 initial guess on how spi work but not tested
2026-04-13 untested SPI code
2026-04-13 untested new git hooks that fix rebasing issues
2026-04-14 commiting blinky code
2026-04-14 committing new bms_config.c and old bms_config.h
2026-04-14 Timer Blinky Example
2026-04-14 bms_config with SPI using jacob's example
2026-04-14 rkh - began yml and adding CAN
2026-04-14 Time to commit (VS Code saved my as*, huge thanks to Jacob K.)
2026-04-15 Power Therm overhall, have not been reviewed yet
2026-04-15 fixed suggested edits and moved connector
2026-04-16 Minor redcube schematic changes; added some silkscreen; added production files
2026-04-16 moved e-meter part and moved up GND plane
2026-04-16 fixes for connector to BMS MOBO
2026-04-16 Adapted ADC code to oem library
2026-04-16 fixed a trace
2026-04-16 Modified 1-Wire Traces; Added Final Production Files
2026-04-18 BSPD code of VCU finished except CAN, along with some minor changes in Throttle code of VCU
2026-04-18 RKH - added input of PA4 pin (motor current)
2026-04-18 Precharge-discharge Renaming for BOM
2026-04-18 added pin defintions
2026-04-18 rkh - added CAN, Still need to debug CAN before flashing this code to my pcb
2026-04-18 Power-Therm (Rev. 2) and Git Hooks Script Changes (#25)
2026-04-21 I fixed the build errors (I did the exact same mistakes when doing the ADC lib)
2026-04-22 commiting bms timer implementation
2026-04-23 updated pin layout and charger files, yml file is filler for now
2026-04-23 added build file
2026-04-23 commented out some lcd code
2026-04-23 commented out all LCD aspects, builds succesfully
2026-04-23 Changed some minor software things but at this point I am like 90% sure it is hardware issue
2026-04-24 rkh - firmware done, ready for debugging!
2026-04-25 Commiting angle_sensor code and updating file paths.
2026-04-25 Committing initial angle_sensor code.
2026-04-25 Committing partially complete PWM capture code.
2026-04-25 added ADBMS support files and have new way of trying to communicat ISOSPI, still unable to recieve signals
2026-04-26 Add MCP25625 library
2026-04-26 spi is working but I cannot git values of IsoSpi but when I plug the MISO and MOSI on the STM it mirrors values so I'm guessing hardware issue
2026-04-27 commiting missing functions in bms.c based on mkvii and copied over tasks folder from mkvii
2026-04-27 CAN API: Update README
2026-04-27 CAN API: README Formatting
2026-04-27 CAN API README (#26)
2026-04-28 commiting utils folder
2026-04-30 most recent firmware
2026-04-30 Some changes during hardware testing
2026-05-01 Firmware update, CAN doesnt work at this stage, may or may not be my firmware
2026-05-02 Worked for 16s Merge BSPD and throttle VCU firmware
    Consolidate the separate BSPD and throttle VCU firmware into a single VCU
    target with shared GPIO, ADC, and runtime state.
    Add combined fault handling for APPS, brake/throttle implausibility, BSPD
    latch, BSPD shutdown sense, and inertia switch sense. Split shutdown-chain
    GPIO reads into vcu_read_shutdown_chain_1ms() and feed the resulting closed
    states into the fault manager.
2026-05-07 Merged Throttle and BSPD firmware, implemented CAN functions, ready to test
2026-05-08 lowkey not too sure what changed
2026-05-10 Updated VCU Kicad including both schematics and layout according to changes that had been made during hardware testing: removed R15, changed R14 to 0 ohm
2026-05-12 Added more comments (docstrings) to the code
2026-05-23 Updated KiCad Parts Library
2026-05-23 Removed Duplicate KiCad Files and kicad_wks file
2026-05-24 Standardized Folder Names
2026-05-24 Moved examples to example folder; removed outdated example
2026-05-24 Restored Working Version of Brake Temperature Sensor Project Schematics
2026-05-26 Fixed Path Error in Example DBC Generator BUILD File
2026-06-05 Replaced TO247.wrl with TO247.step 3D model to work well with Git LFS and associated changes
2026-06-06 Added OEM Info Footprint
2026-06-15 add .history folder to .gitignore
2026-06-15 Layout Draft 1
2026-06-22 Layout v2
2026-06-24 Layout Draft 3
2026-06-28 final tweeks
